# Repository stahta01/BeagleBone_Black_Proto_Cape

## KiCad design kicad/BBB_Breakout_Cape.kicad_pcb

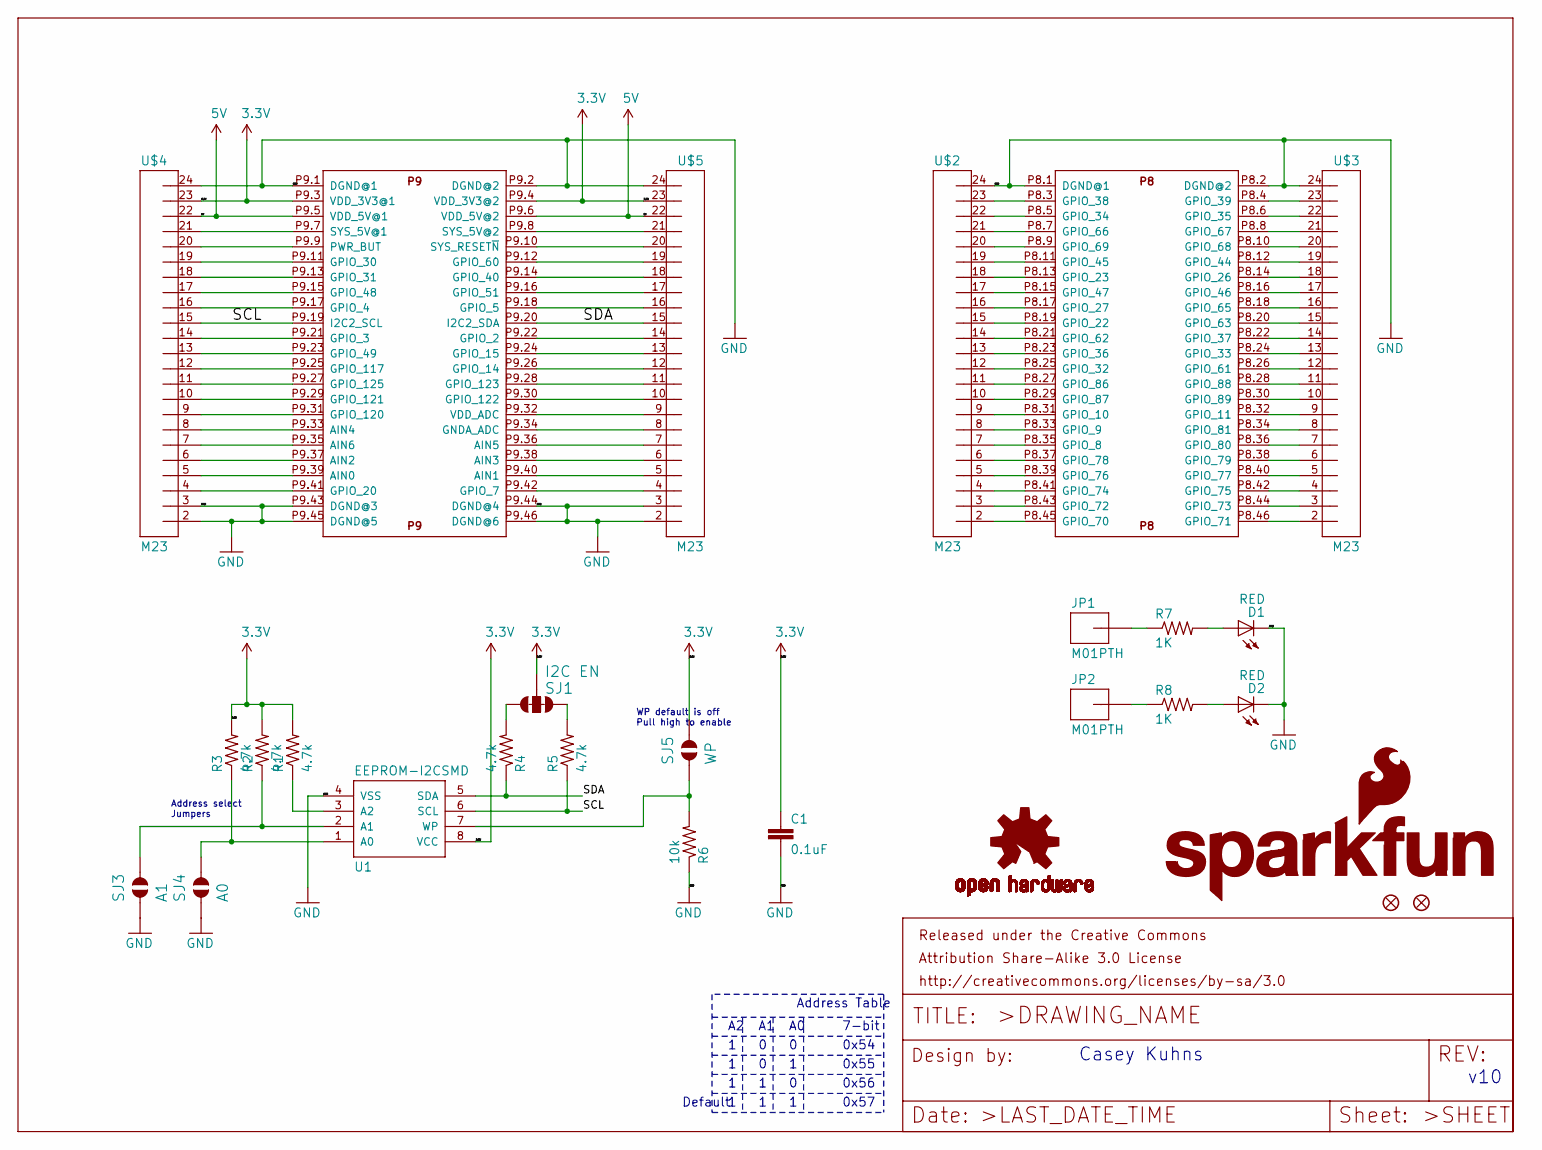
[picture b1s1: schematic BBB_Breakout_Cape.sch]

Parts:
C1: 0.1uF; 0603-CAP
D1, D2: RED; LED-0603
FID1, FID2: FIDUCIAL1X2; FIDUCIAL-1X2
FRAME1: FRAME-LETTER; CREATIVE_COMMONS
JP1, JP2: M01PTH; 1X01
LOGO2: OSHW-LOGOS; OSHW-LOGO-S
LOGO3: SFE_LOGO_NAME_FLAME.1_INCH; SFE_LOGO_NAME_FLAME_.1
R1, R2, R3, R4, R5: 4.7k; 0603@1
R6: 10k; 0603-RES
R7, R8: 1K; 0603-RES
SJ1: I2C EN; SMT-JUMPER_3_2-NC_PASTE_SILK
SJ3: A1; SMT-JUMPER_2_NO_SILK
SJ4: A0; SMT-JUMPER_2_NO_SILK
SJ5: WP; SMT-JUMPER_2_NO_SILK
U1: EEPROM-I2CSMD; SO08
U$1: BEAGLE_BONE_BLACK_CAPE
U$2, U$3, U$4, U$5: M23; 1X23

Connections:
3.3V: C1.1, R1.2, R2.2, R3.2, SJ1.2, SJ5.2, U1.8 (VCC), U$1.P9.3 (VDD_3V3@1), U$1.P9.4 (VDD_3V3@2), U$4.23, U$5.23
5V: U$1.P9.5 (VDD_5V@1), U$1.P9.6 (VDD_5V@2), U$4.22, U$5.22
/SCL: R5.1, U1.6 (SCL), U$1.P9.19 (I2C2_SCL), U$4.15
/SDA: R4.1, U1.5 (SDA), U$1.P9.20 (I2C2_SDA), U$5.15
GND: C1.2, D1.C, D2.C, R6.1, SJ3.1, SJ4.1, U1.4 (VSS), U$1.P8.1 (DGND@1), U$1.P8.2 (DGND@2), U$1.P9.1 (DGND@1), U$1.P9.2 (DGND@2), U$1.P9.43 (DGND@3), U$1.P9.44 (DGND@4), U$1.P9.45 (DGND@5), U$1.P9.46 (DGND@6), U$2.24, U$3.24, U$4.2, U$4.3, U$4.24, U$5.2, U$5.3, U$5.24
unnamed: D1.A, R7.2
unnamed: D2.A, R8.2
unnamed: JP1.1, R7.1
unnamed: JP2.1, R8.1
unnamed: R1.1, U1.3 (A2)
unnamed: R2.1, SJ3.2, U1.2 (A1)
unnamed: R3.1, SJ4.2, U1.1 (A0)
unnamed: R4.2, SJ1.3
unnamed: R5.2, SJ1.1
unnamed: R6.2, SJ5.1, U1.7 (WP)
unnamed: U$1.P8.3 (GPIO_38), U$2.23
unnamed: U$1.P8.4 (GPIO_39), U$3.23
unnamed: U$1.P8.5 (GPIO_34), U$2.22
unnamed: U$1.P8.6 (GPIO_35), U$3.22
unnamed: U$1.P8.7 (GPIO_66), U$2.21
unnamed: U$1.P8.8 (GPIO_67), U$3.21
unnamed: U$1.P8.9 (GPIO_69), U$2.20
unnamed: U$1.P8.10 (GPIO_68), U$3.20
unnamed: U$1.P8.11 (GPIO_45), U$2.19
unnamed: U$1.P8.12 (GPIO_44), U$3.19
unnamed: U$1.P8.13 (GPIO_23), U$2.18
unnamed: U$1.P8.14 (GPIO_26), U$3.18
unnamed: U$1.P8.15 (GPIO_47), U$2.17
unnamed: U$1.P8.16 (GPIO_46), U$3.17
unnamed: U$1.P8.17 (GPIO_27), U$2.16
unnamed: U$1.P8.18 (GPIO_65), U$3.16
unnamed: U$1.P8.19 (GPIO_22), U$2.15
unnamed: U$1.P8.20 (GPIO_63), U$3.15
unnamed: U$1.P8.21 (GPIO_62), U$2.14
unnamed: U$1.P8.22 (GPIO_37), U$3.14
unnamed: U$1.P8.23 (GPIO_36), U$2.13
unnamed: U$1.P8.24 (GPIO_33), U$3.13
unnamed: U$1.P8.25 (GPIO_32), U$2.12
unnamed: U$1.P8.26 (GPIO_61), U$3.12
unnamed: U$1.P8.27 (GPIO_86), U$2.11
unnamed: U$1.P8.28 (GPIO_88), U$3.11
unnamed: U$1.P8.29 (GPIO_87), U$2.10
unnamed: U$1.P8.30 (GPIO_89), U$3.10
unnamed: U$1.P8.31 (GPIO_10), U$2.9
unnamed: U$1.P8.32 (GPIO_11), U$3.9
unnamed: U$1.P8.33 (GPIO_9), U$2.8
unnamed: U$1.P8.34 (GPIO_81), U$3.8
unnamed: U$1.P8.35 (GPIO_8), U$2.7
unnamed: U$1.P8.36 (GPIO_80), U$3.7
unnamed: U$1.P8.37 (GPIO_78), U$2.6
unnamed: U$1.P8.38 (GPIO_79), U$3.6
unnamed: U$1.P8.39 (GPIO_76), U$2.5
unnamed: U$1.P8.40 (GPIO_77), U$3.5
unnamed: U$1.P8.41 (GPIO_74), U$2.4
unnamed: U$1.P8.42 (GPIO_75), U$3.4
unnamed: U$1.P8.43 (GPIO_72), U$2.3
unnamed: U$1.P8.44 (GPIO_73), U$3.3
unnamed: U$1.P8.45 (GPIO_70), U$2.2
unnamed: U$1.P8.46 (GPIO_71), U$3.2
unnamed: U$1.P9.7 (SYS_5V@1), U$4.21
unnamed: U$1.P9.8 (SYS_5V@2), U$5.21
unnamed: U$1.P9.9 (PWR_BUT), U$4.20
unnamed: U$1.P9.10 (SYS_RESET~N), U$5.20
unnamed: U$1.P9.11 (GPIO_30), U$4.19
unnamed: U$1.P9.12 (GPIO_60), U$5.19
unnamed: U$1.P9.13 (GPIO_31), U$4.18
unnamed: U$1.P9.14 (GPIO_40), U$5.18
unnamed: U$1.P9.15 (GPIO_48), U$4.17
unnamed: U$1.P9.16 (GPIO_51), U$5.17
unnamed: U$1.P9.17 (GPIO_4), U$4.16
unnamed: U$1.P9.18 (GPIO_5), U$5.16
unnamed: U$1.P9.21 (GPIO_3), U$4.14
unnamed: U$1.P9.22 (GPIO_2), U$5.14
unnamed: U$1.P9.23 (GPIO_49), U$4.13
unnamed: U$1.P9.24 (GPIO_15), U$5.13
unnamed: U$1.P9.25 (GPIO_117), U$4.12
unnamed: U$1.P9.26 (GPIO_14), U$5.12
unnamed: U$1.P9.27 (GPIO_125), U$4.11
unnamed: U$1.P9.28 (GPIO_123), U$5.11
unnamed: U$1.P9.29 (GPIO_121), U$4.10
unnamed: U$1.P9.30 (GPIO_122), U$5.10
unnamed: U$1.P9.31 (GPIO_120), U$4.9
unnamed: U$1.P9.32 (VDD_ADC), U$5.9
unnamed: U$1.P9.33 (AIN4), U$4.8
unnamed: U$1.P9.34 (GNDA_ADC), U$5.8
unnamed: U$1.P9.35 (AIN6), U$4.7
unnamed: U$1.P9.36 (AIN5), U$5.7
unnamed: U$1.P9.37 (AIN2), U$4.6
unnamed: U$1.P9.38 (AIN3), U$5.6
unnamed: U$1.P9.39 (AIN0), U$4.5
unnamed: U$1.P9.40 (AIN1), U$5.5
unnamed: U$1.P9.41 (GPIO_20), U$4.4
unnamed: U$1.P9.42 (GPIO_7), U$5.4

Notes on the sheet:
Address Table
Default
7-bit
0x54
0x56
0x55
0x57
Casey Kuhns
v10
WP default is off Pull high to enable
Address select Jumpers

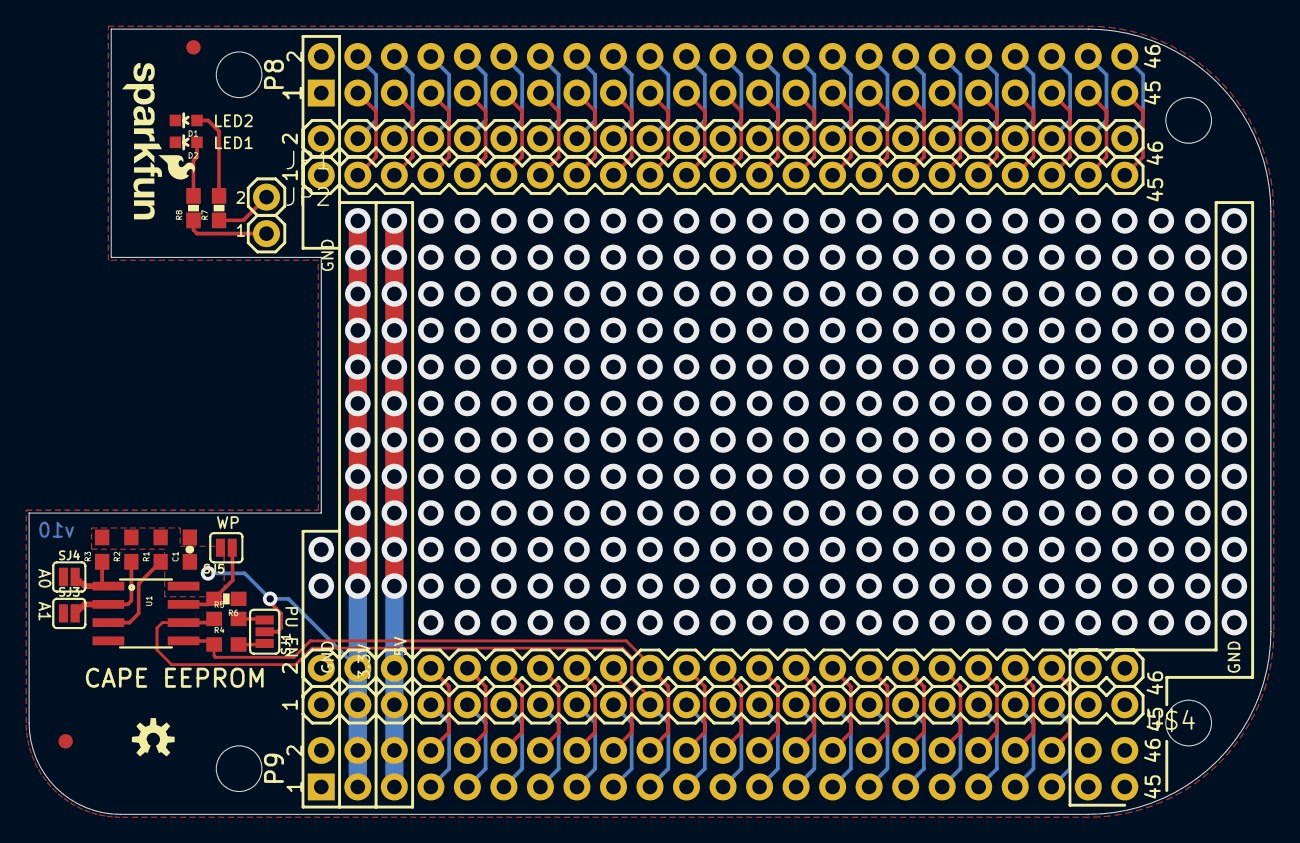
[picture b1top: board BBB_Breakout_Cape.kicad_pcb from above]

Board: 2 copper layers, 86.4 x 54.6 mm, 29 parts (0 on the bottom side), 93 nets.

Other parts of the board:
U$6: SFE_LOGO_NAME_FLAME_.1

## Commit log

2022-04-27 git: Add kicad ignore file
2022-04-27 kicad: Add kicad import created project files

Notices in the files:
parts and their libraries:
Released under the Creative Commons Attribution Share-Alike 3.0 License
